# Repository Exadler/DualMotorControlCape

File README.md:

DualMotorControlCape (DMCC)
===========================

Dual Motor H-Bridge with dual Quadrature Encoder cape for BeagleBone Black

Follow our progress on http://exadler.blogspot.com and http://www.exadler.com

Features:
---------

* Two Motors Supported
* Two Quadrature Encoders Supported
* Up to 7A continuous current, 15A peak
* 5V to 28V motors
* 18KHz PWM for quiet operation
* I2C Interface to the Beaglebone Black
* Stackable, up to 4 DMCC can be put on a single Beaglebone (8 motors!)
* Optional PID position and velocity with adjustable Kp,Ki,Kd
* Control through open source C library
* Reverse / Forward LED indicators on each motor
* Current sensor for each motor

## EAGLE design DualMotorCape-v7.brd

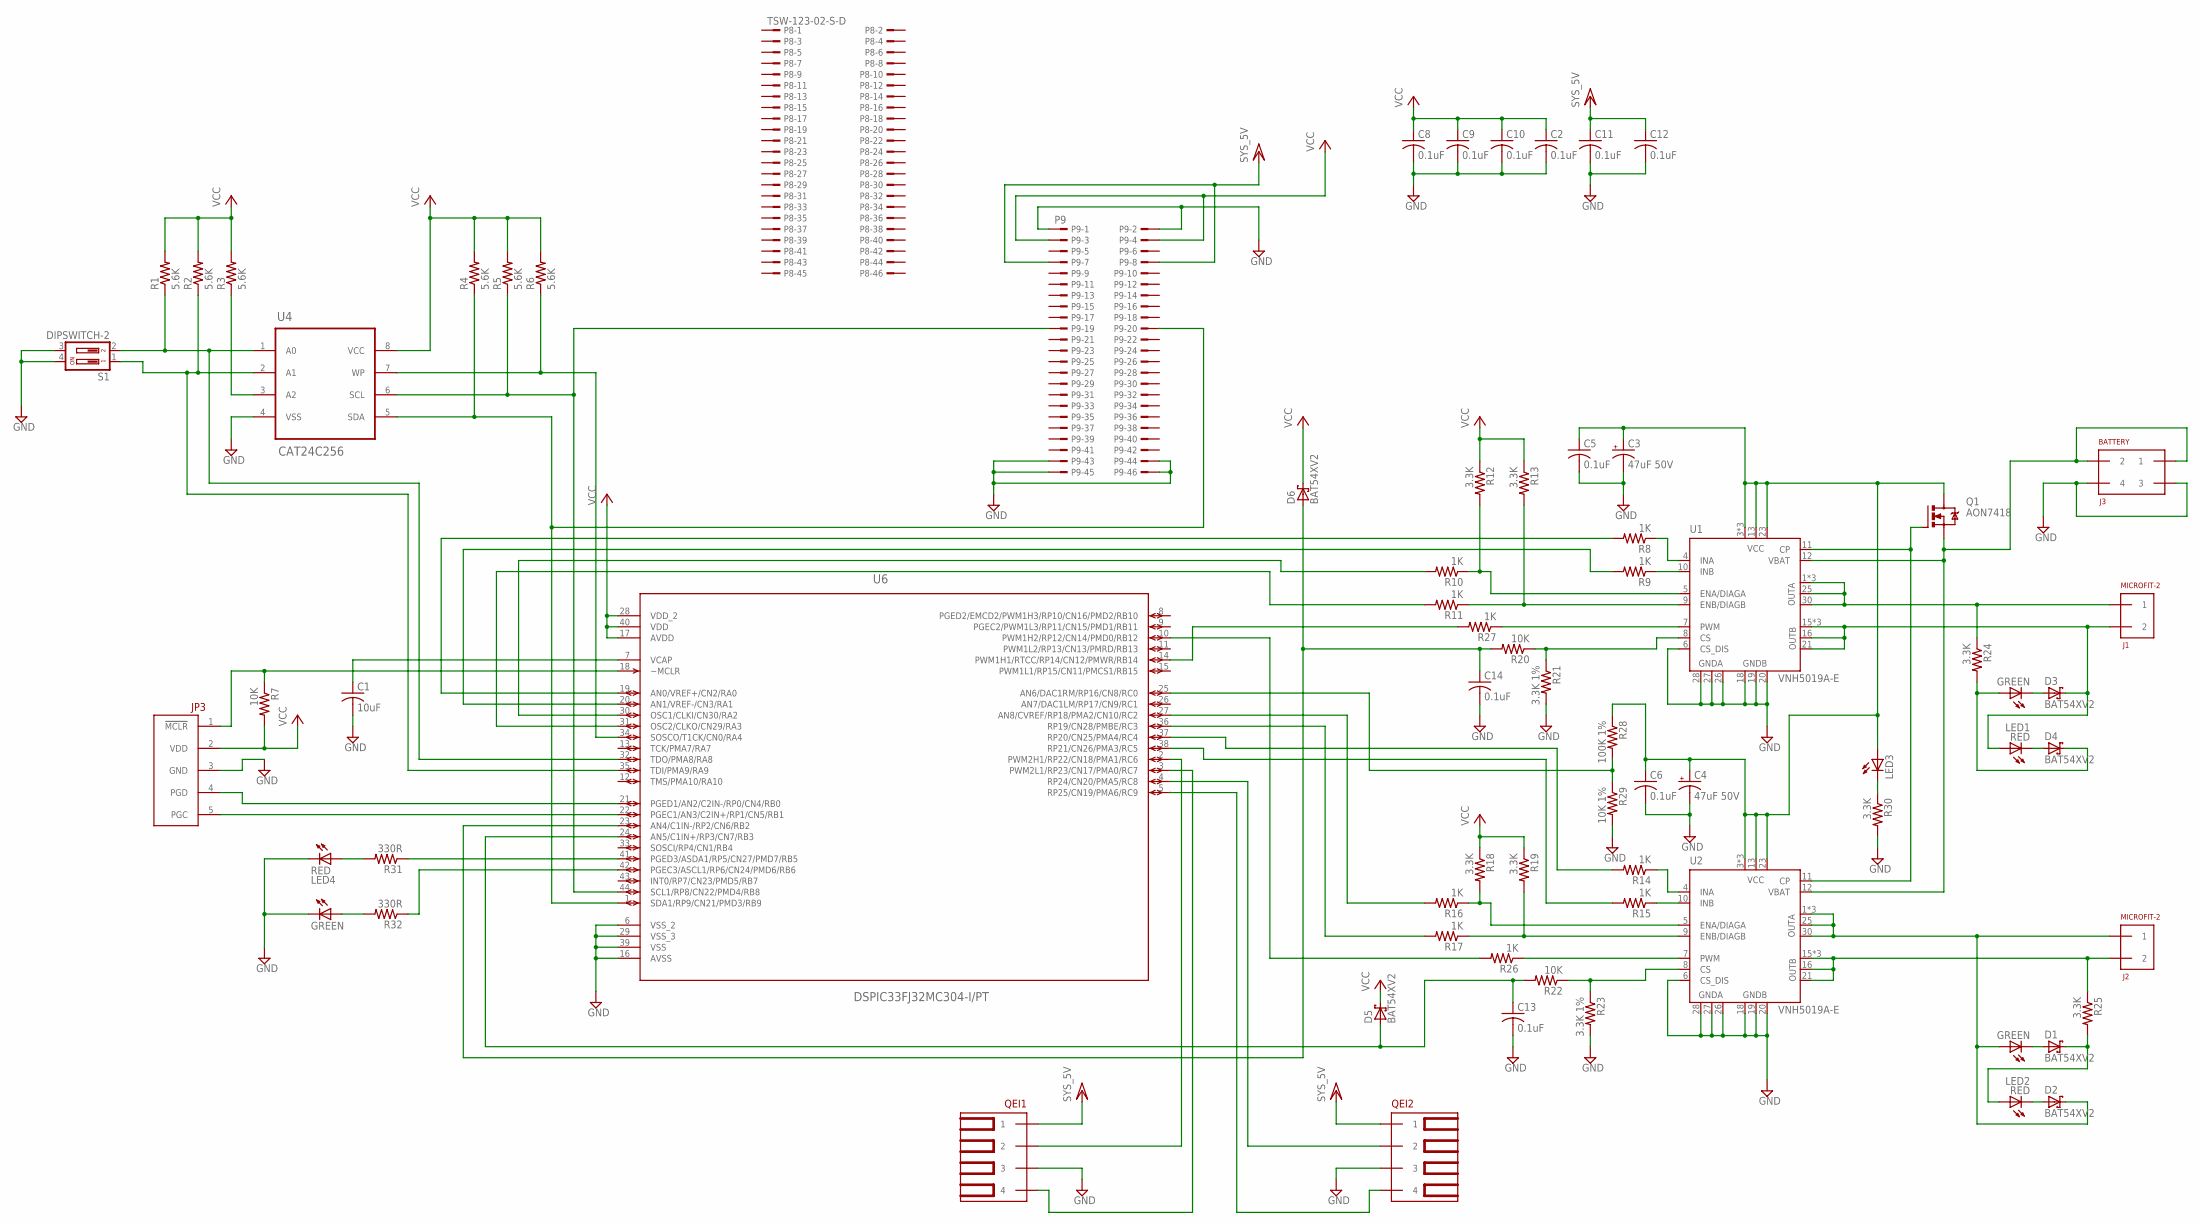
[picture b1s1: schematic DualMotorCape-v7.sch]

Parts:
C1: 10uF; C0805; MPN 08056C106KAT2A
C2, C5, C6, C8, C9, C10, C11, C12, C13, C14: 0.1uF; C0603; MPN 06035C104KAT2A
C3, C4: 47uF 50V; UD-8X10_NICHICON; MPN EEE-FK1H470XP; DIGIKEY 493-2303-1-ND
D1, D2, D3, D4, D5, D6: BAT54XV2; SOD523; MPN BAT54XV2; DIGIKEY# BAT54XV2CT-ND
J1, J2: MICROFIT-2; MICROFIT-2-R-TH
J3: BATTERY; MICROFIT-4-R-TH
JP3: ICD2/3-HEADER
LED1, LED2, LED4: KINGBRIGHT-BI-COLOR-LED; LED-1.6X1.5MM-BI-COLOR
LED3: LED-LNJP12X8ARA; LED-603-PANASONIC
P8: TSW-123-02-S-D
P9: P9; TSW-123-02-S-D
Q1: AON7418; DFN3.3X3.3
QEI1, QEI2: MOLEX-KK-22-15-2046-4PIN
R1, R2, R3, R4, R5, R6: 5.6K; R0603; MPN MC 0.063W 0603 1% 5K6
R7, R20, R22: 10K; R0603
R8, R9, R10, R11, R14, R15, R16, R17, R26, R27: 1K; R0603
R12, R13, R18, R19, R24, R25, R30: 3.3K; R0603; MPN CRCW06033K30FKEA
R21, R23: 3.3K 1%; R0603; MPN CRCW06033K30FKEA
R28: 100K 1%; R0603; MPN ASC0603-100KFT5
R29: 10K 1%; R0603; MPN CRCW060310K0FKTA
R31, R32: 330R; R0603
S1: DIPSWITCH-2; DIPSWITCH-218-2; DIGIKEY# CT2182LPST-ND
U1, U2: VNH5019A-E; MPN VNH5019A-E
U4: CAT24C256; SOIC-8; MPN CAT24C256WI-G
U6: DSPIC33FJ32MC304-I/PT; QFP80P1200X1200X120-44N; MPN DSPIC33FJ32MC304-I/PT

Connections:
GND: C1.2, C2.2, C3.-, C4.-, C5.2, C6.2, C8.2, C9.2, C10.2, C11.2, C12.2, C13.2, C14.2, J3.3 (4), J3.4 (3), JP3.3 (GND), LED4.2, LED4.4, P9.1, P9.2, P9.43, P9.44, P9.45, P9.46, QEI1.P$3 (3), QEI2.P$3 (3), R21.2, R23.2, R29.2, R30.2, S1.3, S1.4, U1.6 (CS_DIS), U1.18 (GNDB), U1.19 (GNDB), U1.20 (GNDB), U1.26 (GNDA), U1.27 (GNDA), U1.28 (GNDA), U2.6 (CS_DIS), U2.18 (GNDB), U2.19 (GNDB), U2.20 (GNDB), U2.26 (GNDA), U2.27 (GNDA), U2.28 (GNDA), U4.4 (VSS), U6.6 (VSS_2), U6.16 (AVSS), U6.29 (VSS_3), U6.39 (VSS)
M1+: J1.2 (1), R24.1, U1.1 (OUTA), U1.25 (OUTA), U1.30 (OUTA), U1.NC/OUTA (OUTA), U1.NC/OUTA@1 (OUTA)
M1-: D3.C, J1.1 (2), LED1.1, U1.15 (OUTB), U1.16 (OUTB), U1.21 (OUTB), U1.NC/OUTB (OUTB), U1.NC/OUTB@1 (OUTB)
M2+: D2.C, J2.2 (1), LED2.3, U2.1 (OUTA), U2.25 (OUTA), U2.30 (OUTA), U2.NC/OUTA (OUTA), U2.NC/OUTA@1 (OUTA)
M2-: J2.1 (2), R25.1, U2.15 (OUTB), U2.16 (OUTB), U2.21 (OUTB), U2.NC/OUTB (OUTB), U2.NC/OUTB@1 (OUTB)
unnamed: D4.C, LED1.3, R24.2
unnamed: LED3.2 (C), R30.1
unnamed: LED4.1, R31.2
unnamed: Q1.4 (G), U1.11 (CP), U2.11 (CP)
unnamed: LED4.3, R32.2
unnamed: JP3.1 (!MCLR), R7.1, U6.18 (~MCLR)
unnamed: R31.1, U6.41 (PGED3/ASDA1/RP5/CN27/PMD7/RB5)
unnamed: D3.A, LED1.4
unnamed: R3.1, U4.3 (A2)
unnamed: R6.1, U4.7 (WP), U6.34 (SOSCO/T1CK/CN0/RA4)
unnamed: P9.19, R5.1, U4.6 (SCL), U6.44 (SCL1/RP8/CN22/PMD4/RB8)
unnamed: P9.20, R4.1, U4.5 (SDA), U6.1 (SDA1/RP9/CN21/PMD3/RB9)
unnamed: JP3.5 (PGC), U6.22 (PGEC1/AN3/C2IN+/RP1/CN5/RB1)
unnamed: R32.1, U6.42 (PGEC3/ASCL1/RP6/CN24/PMD6/RB6)
unnamed: JP3.4 (PGD), U6.21 (PGED1/AN2/C2IN-/RP0/CN4/RB0)
unnamed: R11.1, R13.2, U1.9 (ENB/DIAGB)
unnamed: R10.1, R12.2, U1.5 (ENA/DIAGA)
unnamed: R27.2, U6.14 (PWM1H1/RTCC/RP14/CN12/PMWR/RB14)
unnamed: R8.1, U1.4 (INA)
unnamed: R9.1, U1.10 (INB)
unnamed: R15.1, U2.10 (INB)
unnamed: R14.1, U2.4 (INA)
unnamed: R17.2, U6.36 (RP19/CN28/PMBE/RC3)
unnamed: R22.1, R23.1, U2.8 (CS)
unnamed: R20.1, R21.1, U1.8 (CS)
unnamed: R10.2, U6.30 (OSC1/CLKI/CN30/RA2)
unnamed: R11.2, U6.31 (OSC2/CLKO/CN29/RA3)
unnamed: R14.2, U6.37 (RP20/CN25/PMA4/RC4)
unnamed: R15.2, U6.38 (RP21/CN26/PMA3/RC5)
unnamed: R16.2, U6.27 (AN8/CVREF/RP18/PMA2/CN10/RC2)
unnamed: QEI1.P$2 (2), U6.2 (PWM2H1/RP22/CN18/PMA1/RC6)
unnamed: QEI1.P$4 (4), U6.3 (PWM2L1/RP23/CN17/PMA0/RC7)
unnamed: R26.1, U2.7 (PWM)
unnamed: R28.2, R29.1, U6.25 (AN6/DAC1RM/RP16/CN8/RC0)
unnamed: D1.A, LED2.4
unnamed: R27.1, U1.7 (PWM)
unnamed: C1.1, U6.7 (VCAP)
unnamed: C3.+, C4.+, C5.1, C6.1, LED3.1 (A), Q1.5 (D), Q1.6 (D), Q1.7 (D), Q1.8 (D), Q1.9 (D), R28.1, U1.3 (VCC), U1.13 (VCC), U1.23 (VCC), U1.NC/VCC (VCC), U1.NC/VCC@1 (VCC), U2.3 (VCC), U2.13 (VCC), U2.23 (VCC), U2.NC/VCC (VCC), U2.NC/VCC@1 (VCC)
unnamed: D4.A, LED1.2
unnamed: D2.A, LED2.2
unnamed: D1.C, LED2.1, R25.2
PWM1H2: R26.2, U6.10 (PWM1H2/RP12/CN14/PMD0/RB12)
RA0: R8.2, U6.19 (AN0/VREF+/CN2/RA0)
RA1: R9.2, U6.20 (AN1/VREF-/CN3/RA1)
RB2: C14.1, D6.A, R20.2, U6.23 (AN4/C1IN-/RP2/CN6/RB2)
RB3: C13.1, D5.A, R22.2, U6.24 (AN5/C1IN+/RP3/CN7/RB3)
RB6: QEI2.P$2 (2), U6.4 (RP24/CN20/PMA5/RC8)
RB7: QEI2.P$4 (4), U6.5 (RP25/CN19/PMA6/RC9)
RC8: R1.1, S1.2, U4.1 (A0), U6.32 (TDO/PMA8/RA8)
RC9: R2.1, S1.1, U4.2 (A1), U6.35 (TDI/PMA9/RA9)
U2ENA: R16.1, R18.2, U2.5 (ENA/DIAGA)
U2ENB: R17.1, R19.2, U2.9 (ENB/DIAGB)
VBAT: J3.1 (2), J3.2 (1), Q1.1 (S), Q1.2 (S), Q1.3 (S), U1.12 (VBAT), U2.12 (VBAT)
VCC: C2.1, C8.1, C9.1, C10.1, D5.C, D6.C, JP3.2 (VDD), P9.3, P9.4, R1.2, R2.2, R3.2, R4.2, R5.2, R6.2, R7.2, R12.1, R13.1, R18.1, R19.1, U4.8 (VCC), U6.17 (AVDD), U6.28 (VDD_2), U6.40 (VDD)
VCC/2: C11.1, C12.1, P9.7, P9.8, QEI1.P$1 (1), QEI2.P$1 (1)

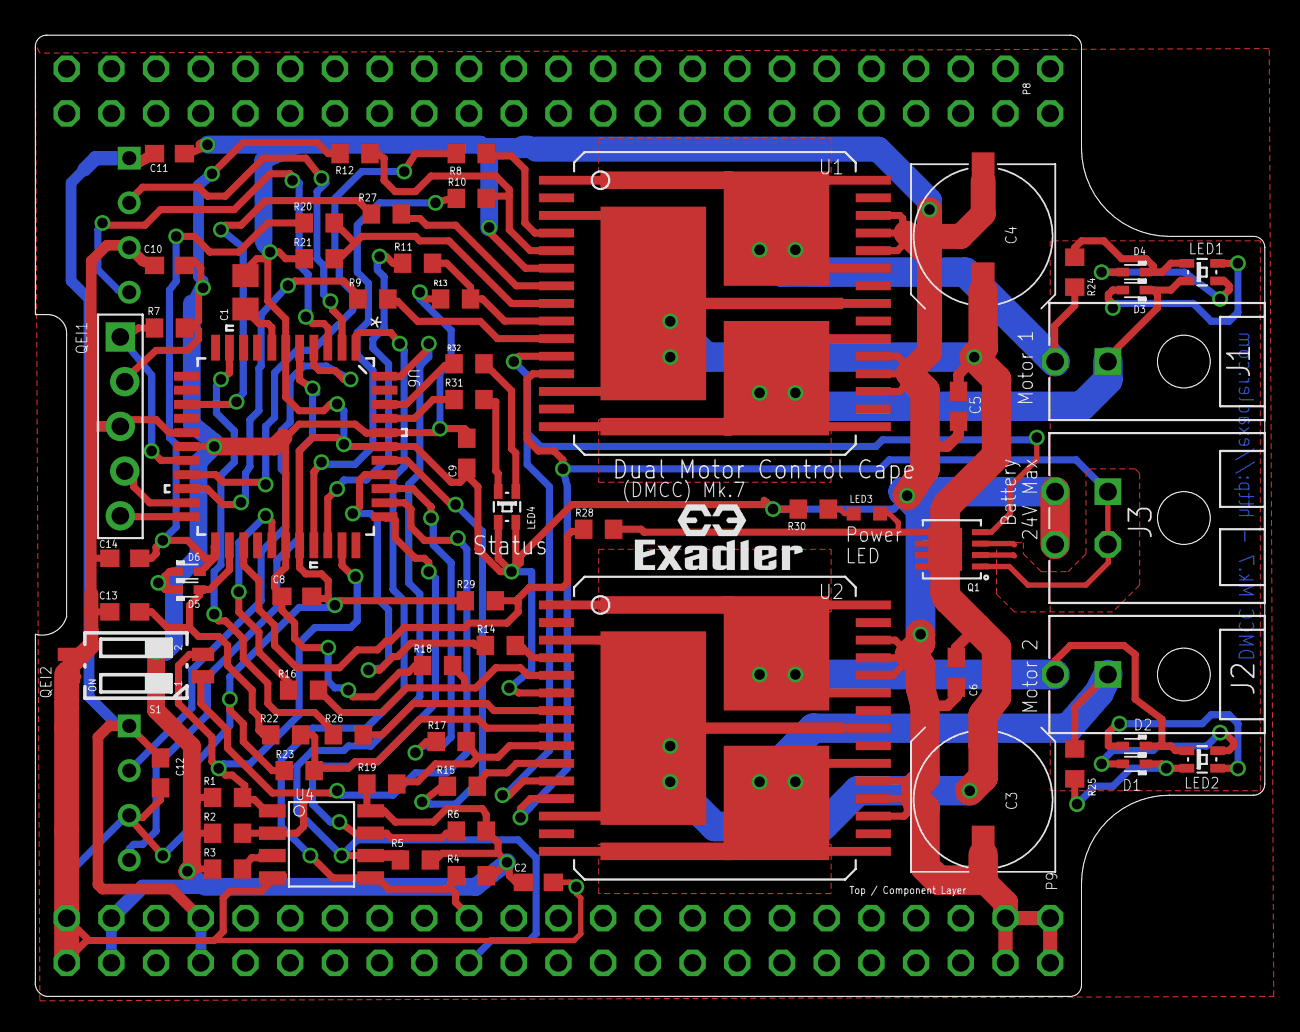
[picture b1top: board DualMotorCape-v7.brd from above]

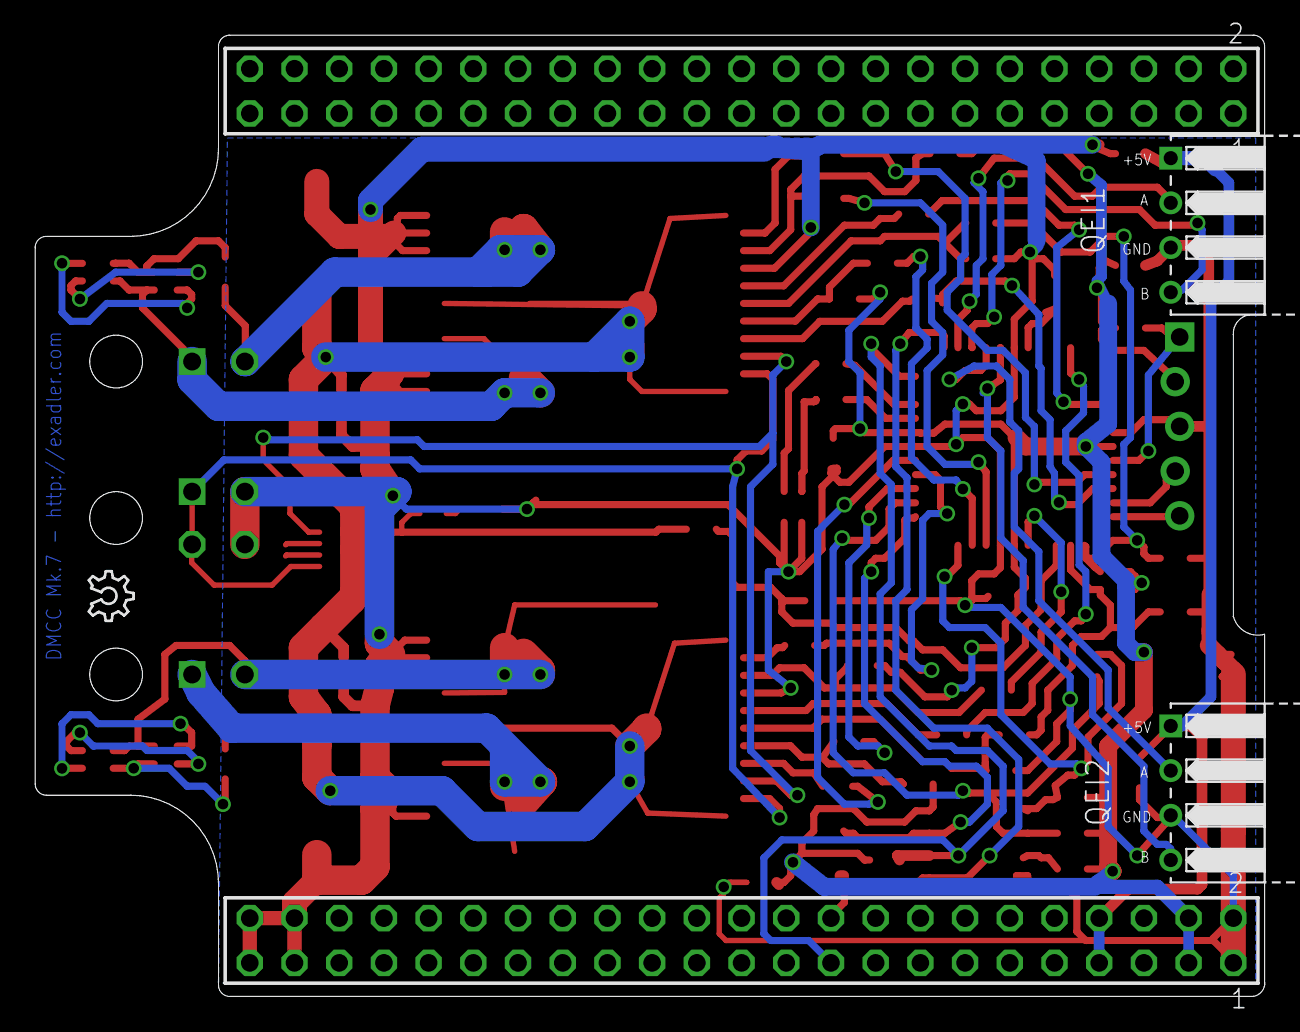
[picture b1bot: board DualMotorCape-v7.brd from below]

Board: 2 copper layers, 69.9 x 54.6 mm, 71 parts (4 on the bottom side), 60 nets.

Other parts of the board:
U$1: EXADLER-LOGO
U$2: OSHW_6X100_NOTEXT

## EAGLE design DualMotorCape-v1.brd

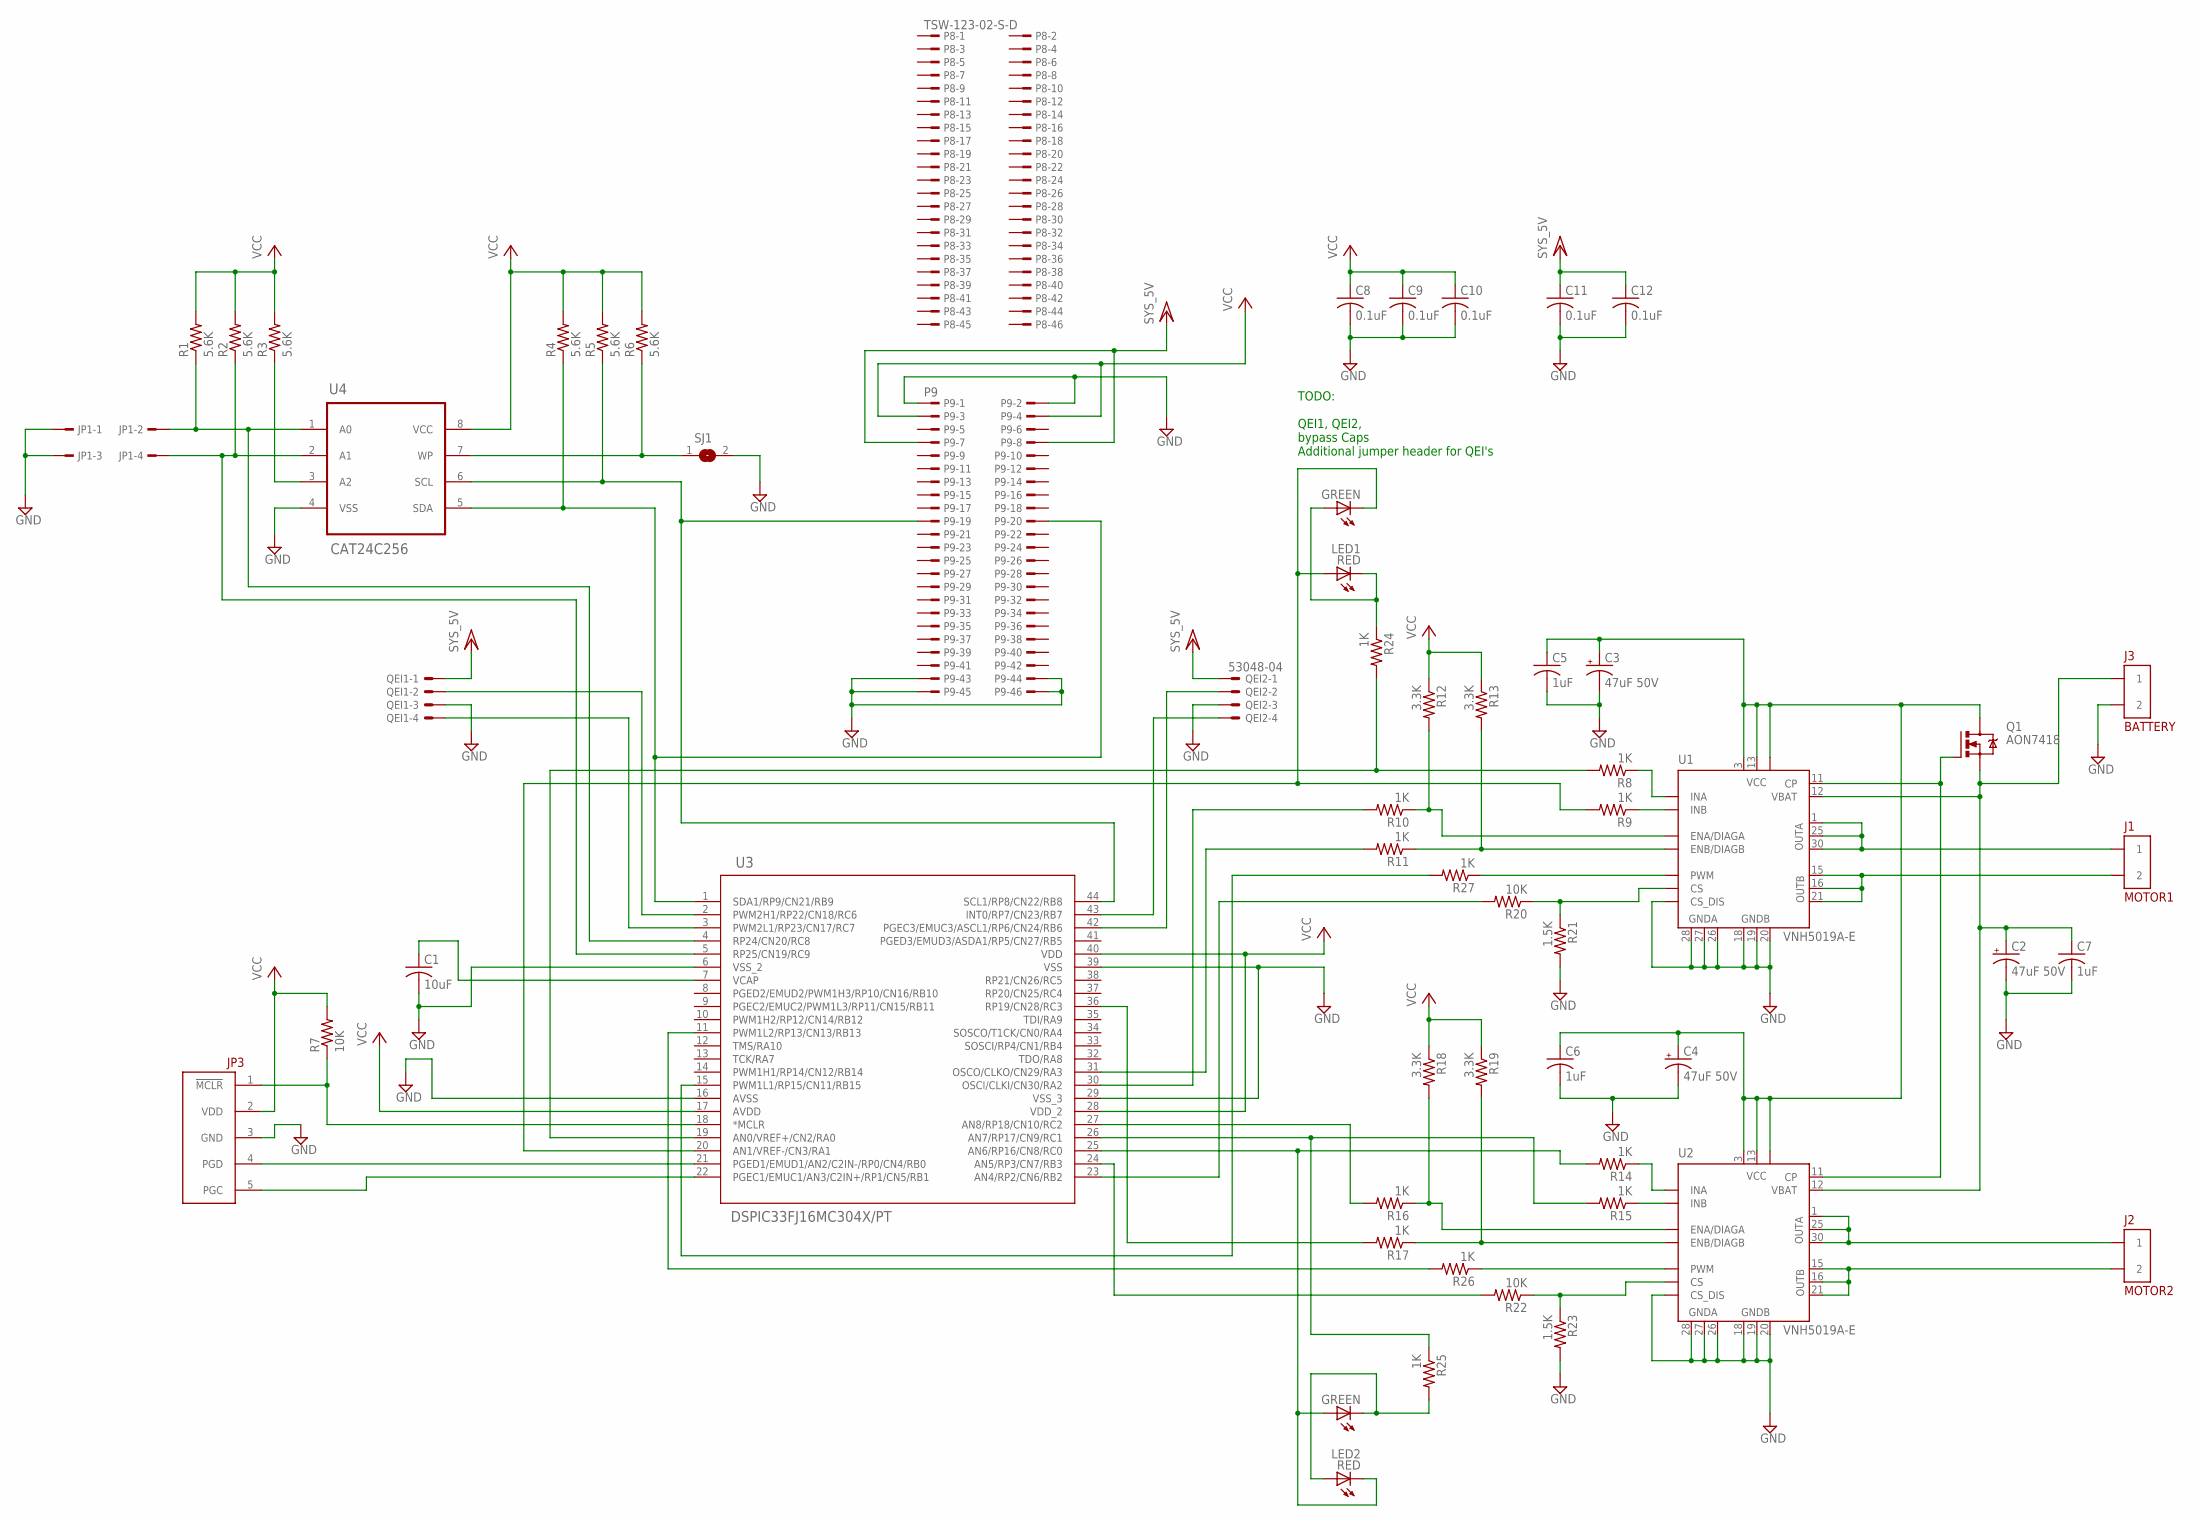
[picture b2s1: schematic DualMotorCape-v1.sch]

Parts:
C1: 10uF; C0805
C2, C3, C4: 47uF 50V; UD-6,3X7,7_NICHICON; DIGIKEY 493-2303-1-ND
C5, C6, C7: 1uF; C0603
C8, C9, C10, C11, C12: 0.1uF; C0603
J1: MOTOR1; TERMINAL-BLOCK-2.54MM-2
J2: MOTOR2; TERMINAL-BLOCK-2.54MM-2
J3: BATTERY; TERMINAL-BLOCK-2.54MM-2
JP1: TSW-102-02-S-D
JP3: ICD2/3-HEADER
LED1, LED2: KINGBRIGHT-BI-COLOR-LED; LED-1.6X1.5MM-BI-COLOR
P8: TSW-123-02-S-D
P9: P9; TSW-123-02-S-D
Q1: AON7418; DFN3.3X3.3
QEI1, QEI2: 53048-04
R1, R2, R3, R4, R5, R6: 5.6K; R0603
R7, R20, R22: 10K; R0603
R8, R9, R10, R11, R14, R15, R16, R17, R24, R25, R26, R27: 1K; R0603
R12, R13, R18, R19: 3.3K; R0603
R21, R23: 1.5K; R0603
SJ1: SJ
U1, U2: VNH5019A-E
U3: DSPIC33FJ16MC304X/PT; TQFP44_MC
U4: CAT24C256; SOIC-8

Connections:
GND: C1.2, C2.-, C3.-, C4.-, C5.2, C6.2, C7.2, C8.2, C9.2, C10.2, C11.2, C12.2, J3.2, JP1.1, JP1.3, JP3.3 (GND), P9.1, P9.2, P9.43, P9.44, P9.45, P9.46, QEI1.3, QEI2.3, R21.2, R23.2, SJ1.2, U1.6 (CS_DIS), U1.18 (GNDB), U1.19 (GNDB), U1.20 (GNDB), U1.26 (GNDA), U1.27 (GNDA), U1.28 (GNDA), U2.6 (CS_DIS), U2.18 (GNDB), U2.19 (GNDB), U2.20 (GNDB), U2.26 (GNDA), U2.27 (GNDA), U2.28 (GNDA), U3.6 (VSS_2), U3.16 (AVSS), U3.29 (VSS_3), U3.39 (VSS), U4.4 (VSS)
unnamed: C2.+, C7.1, J3.1, Q1.1 (S), Q1.2 (S), Q1.3 (S), U1.12 (VBAT), U2.12 (VBAT)
unnamed: J1.1, U1.1 (OUTA), U1.25 (OUTA), U1.30 (OUTA)
unnamed: C3.+, C4.+, C5.1, C6.1, Q1.5 (D), Q1.6 (D), Q1.7 (D), Q1.8 (D), U1.3 (VCC), U1.13 (VCC), U1.23 (VCC), U2.3 (VCC), U2.13 (VCC), U2.23 (VCC)
unnamed: Q1.4 (G), U1.11 (CP), U2.11 (CP)
unnamed: J1.2, U1.15 (OUTB), U1.16 (OUTB), U1.21 (OUTB)
unnamed: JP1.2, R1.1, U3.4 (RP24/CN20/RC8), U4.1 (A0)
unnamed: JP1.4, R2.1, U3.5 (RP25/CN19/RC9), U4.2 (A1)
unnamed: J2.1, U2.1 (OUTA), U2.25 (OUTA), U2.30 (OUTA)
unnamed: J2.2, U2.15 (OUTB), U2.16 (OUTB), U2.21 (OUTB)
unnamed: R3.1, U4.3 (A2)
unnamed: R6.1, SJ1.1, U4.7 (WP)
unnamed: P9.19, R5.1, U3.44 (SCL1/RP8/CN22/RB8), U4.6 (SCL)
unnamed: P9.20, R4.1, U3.1 (SDA1/RP9/CN21/RB9), U4.5 (SDA)
unnamed: JP3.5 (PGC), U3.22 (PGEC1/EMUC1/AN3/C2IN+/RP1/CN5/RB1)
unnamed: JP3.1 (!MCLR), R7.1, U3.18 (*MCLR)
unnamed: JP3.4 (PGD), U3.21 (PGED1/EMUD1/AN2/C2IN-/RP0/CN4/RB0)
unnamed: R26.2, U3.11 (PWM1L2/RP13/CN13/RB13)
unnamed: R11.1, R13.2, U1.9 (ENB/DIAGB)
unnamed: R10.1, R12.2, U1.5 (ENA/DIAGA)
unnamed: R27.2, U3.15 (PWM1L1/RP15/CN11/RB15)
unnamed: R8.1, U1.4 (INA)
unnamed: R9.1, U1.10 (INB)
unnamed: R15.1, U2.10 (INB)
unnamed: R14.1, U2.4 (INA)
unnamed: R17.1, R19.2, U2.9 (ENB/DIAGB)
unnamed: R16.1, R18.2, U2.5 (ENA/DIAGA)
unnamed: R17.2, U3.36 (RP19/CN28/RC3)
unnamed: R22.1, R23.1, U2.8 (CS)
unnamed: R20.1, R21.1, U1.8 (CS)
unnamed: R8.2, R24.2, U3.19 (AN0/VREF+/CN2/RA0)
unnamed: LED1.1, LED1.4, R9.2, U3.20 (AN1/VREF-/CN3/RA1)
unnamed: R10.2, U3.30 (OSCI/CLKI/CN30/RA2)
unnamed: R11.2, U3.31 (OSCO/CLKO/CN29/RA3)
unnamed: R20.2, U3.23 (AN4/RP2/CN6/RB2)
unnamed: LED2.2, LED2.3, R14.2, U3.25 (AN6/RP16/CN8/RC0)
unnamed: R15.2, R25.1, U3.26 (AN7/RP17/CN9/RC1)
unnamed: R16.2, U3.27 (AN8/RP18/CN10/RC2)
unnamed: R22.2, U3.24 (AN5/RP3/CN7/RB3)
unnamed: QEI1.2, U3.2 (PWM2H1/RP22/CN18/RC6)
unnamed: QEI1.4, U3.3 (PWM2L1/RP23/CN17/RC7)
unnamed: QEI2.2, U3.42 (PGEC3/EMUC3/ASCL1/RP6/CN24/RB6)
unnamed: QEI2.4, U3.43 (INT0/RP7/CN23/RB7)
unnamed: R26.1, U2.7 (PWM)
unnamed: LED1.2, LED1.3, R24.1
unnamed: LED2.1, LED2.4, R25.2
unnamed: R27.1, U1.7 (PWM)
unnamed: C1.1, U3.7 (VCAP)
VCC: C8.1, C9.1, C10.1, JP3.2 (VDD), P9.3, P9.4, R1.2, R2.2, R3.2, R4.2, R5.2, R6.2, R7.2, R12.1, R13.1, R18.1, R19.1, U3.17 (AVDD), U3.28 (VDD_2), U3.40 (VDD), U4.8 (VCC)
VCC/2: C11.1, C12.1, P9.7, P9.8, QEI1.1, QEI2.1

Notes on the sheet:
TODO: QEI1, QEI2, bypass Caps Additional jumper header for QEI's

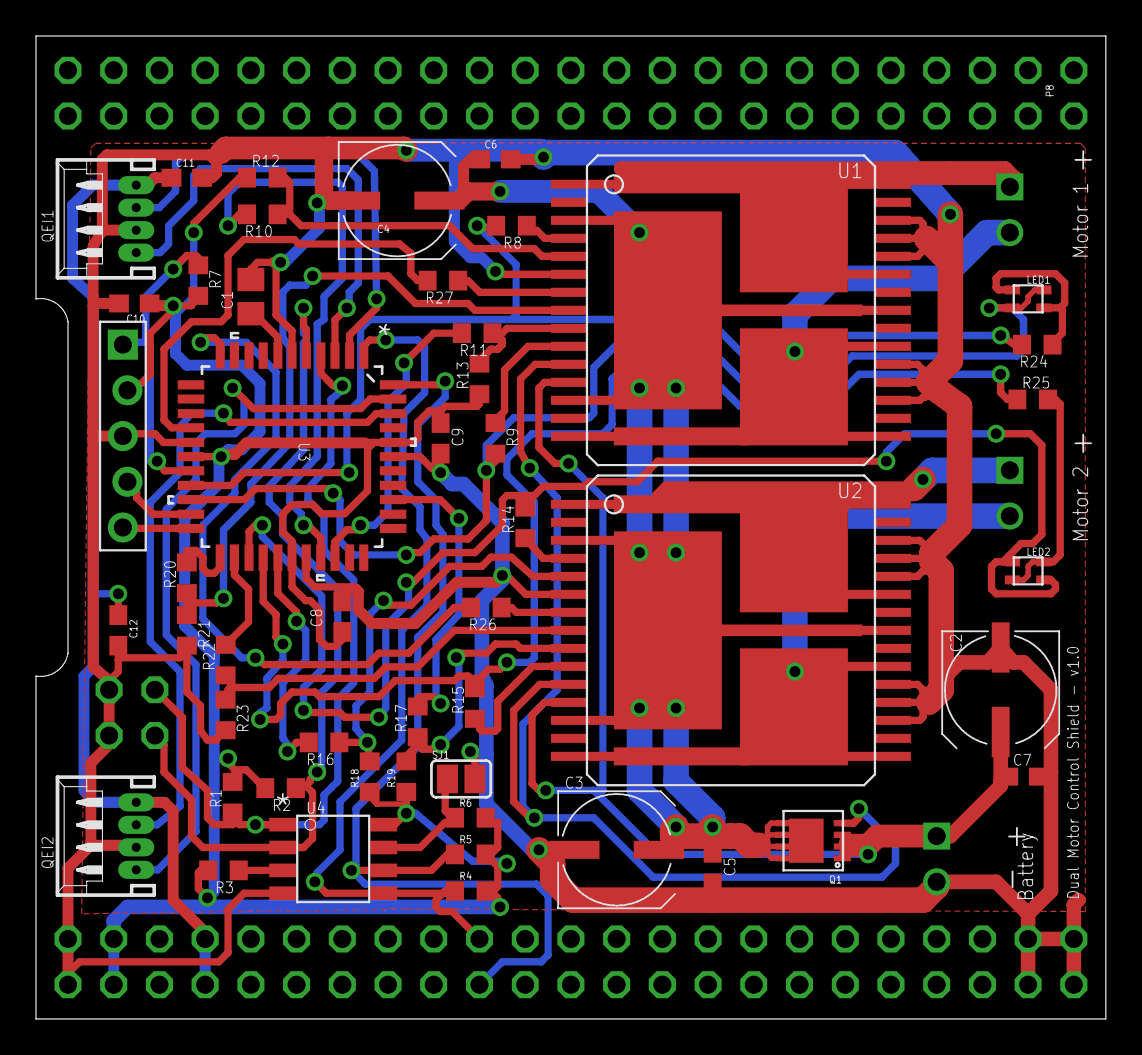
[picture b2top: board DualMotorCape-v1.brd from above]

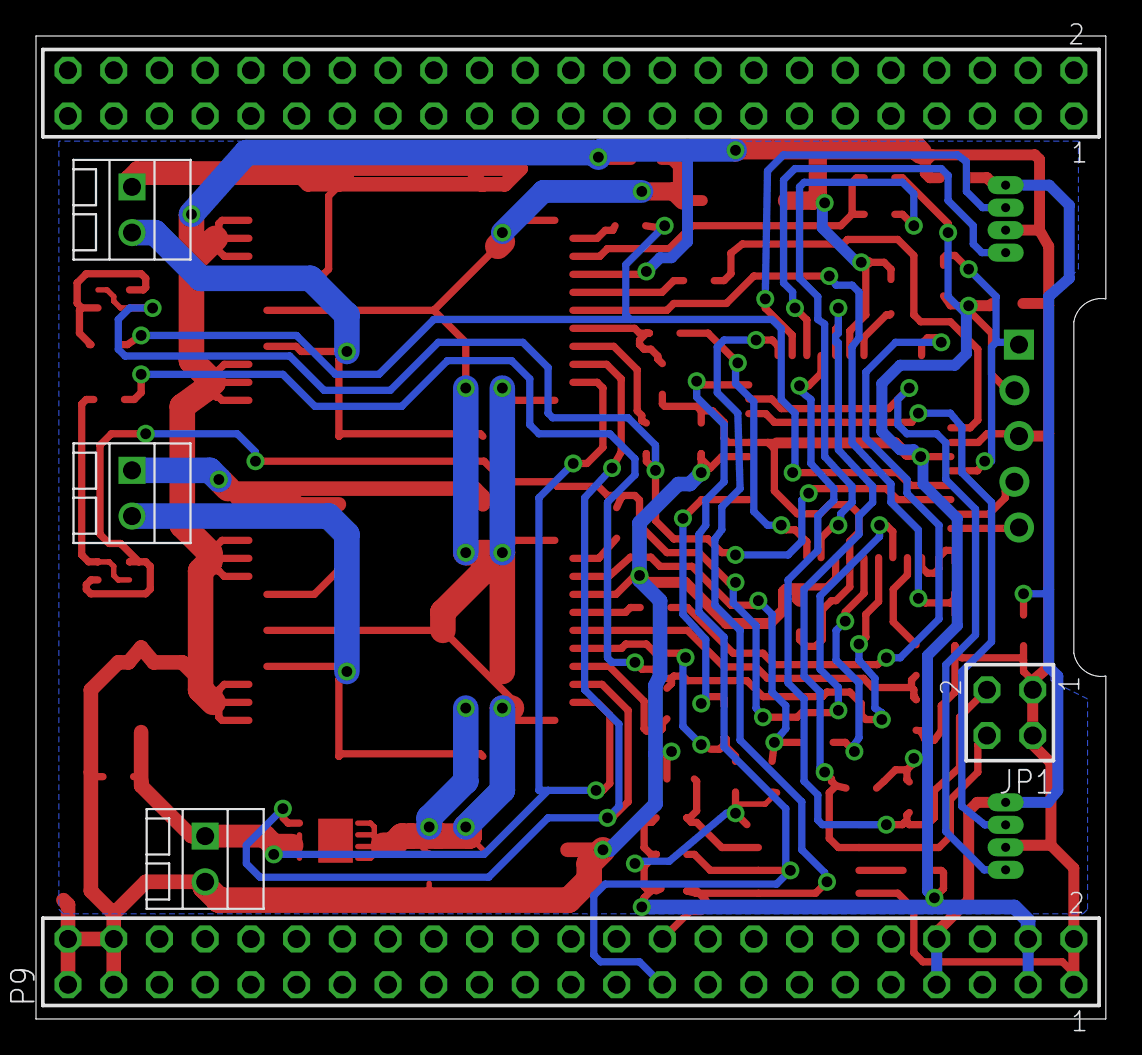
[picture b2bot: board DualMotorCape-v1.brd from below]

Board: 2 copper layers, 59.4 x 54.6 mm, 56 parts (6 on the bottom side), 50 nets.

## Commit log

2012-12-23 Version 1.0
    Release 1.0 of Dual Motor H-Bridge with dual QEI - BeagleBone Cape
2012-12-23 Added PDF of schematic
2012-12-24 Created BOM in .xls format
    Total cost (QTY 100) is 26.4392
2012-12-24 Updated BOM
2013-07-25 DMCC Mk.6 release
2013-07-25 README
2013-07-25 Annotated Image of DMCC
2013-07-25 README update
2016-10-14 V7 files and PDF of schematic
